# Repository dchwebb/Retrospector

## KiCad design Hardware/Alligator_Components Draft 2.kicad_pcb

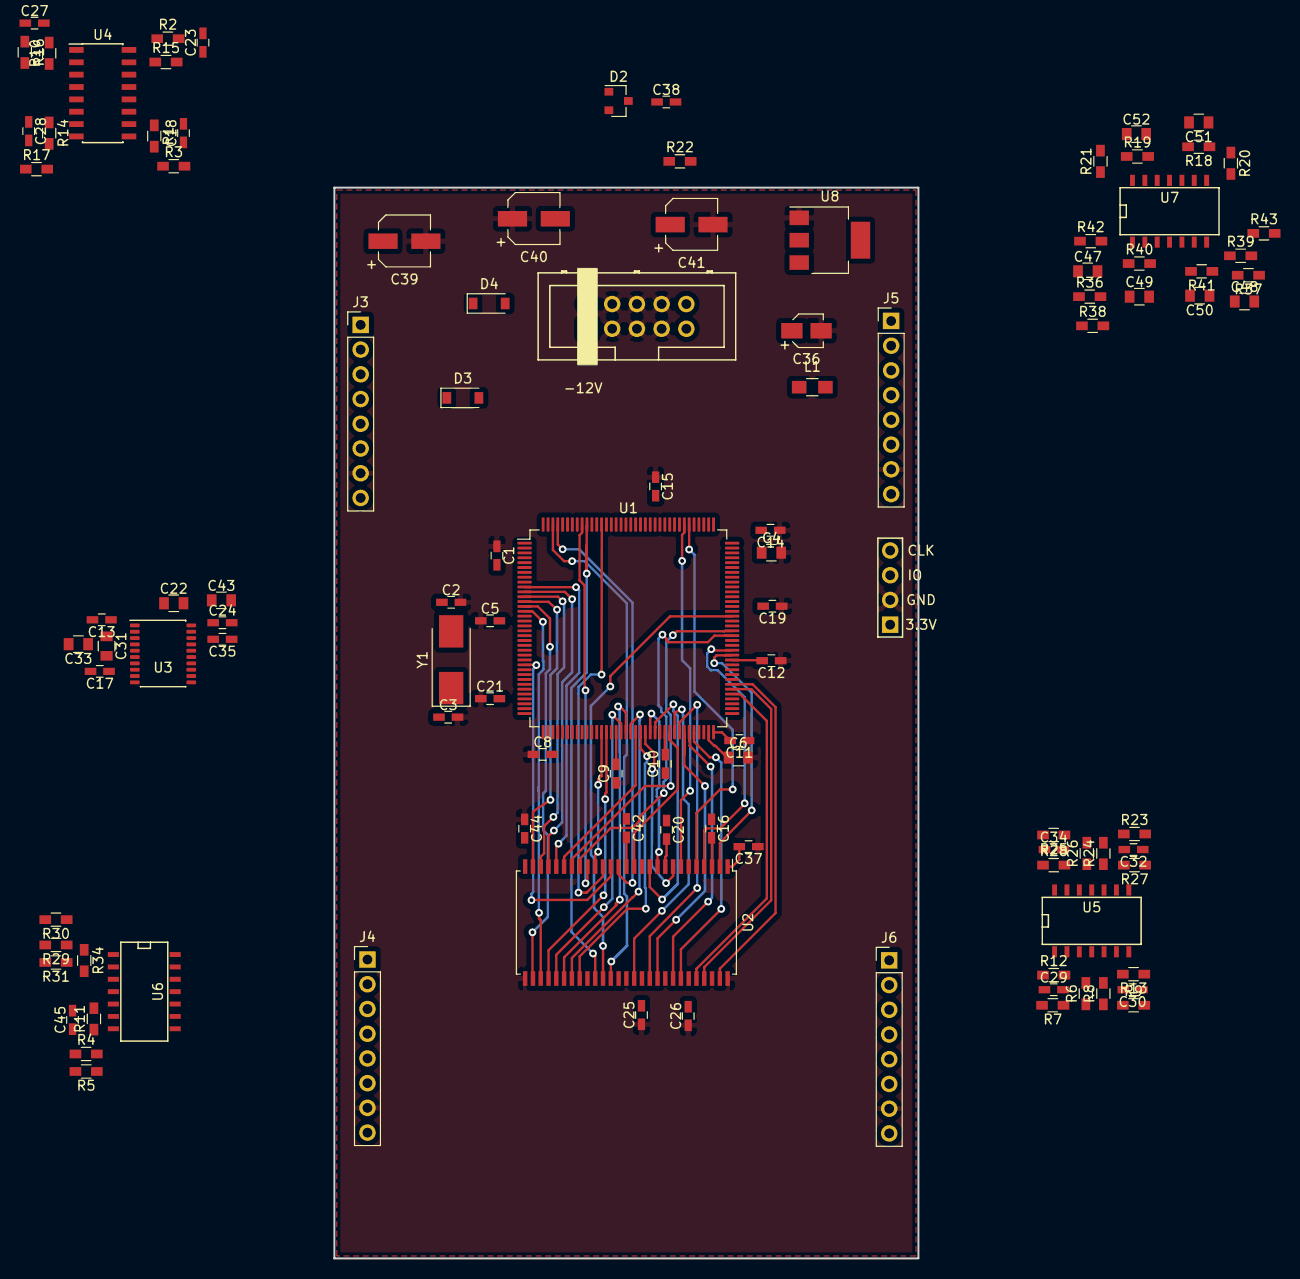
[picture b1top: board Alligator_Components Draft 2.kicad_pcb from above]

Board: 2 copper layers, 60.0 x 110.0 mm, 109 parts (0 on the bottom side), 118 nets.

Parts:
C1, C5, C8, C9, C10, C11, C12, C13, C14, C15, C16, C17, C19, C20, C21, C24, C25, C26, C35, C37, C38, C42, C44: 100nF; C_0603_HandSoldering
C2, C3: 30pF; C_0603_HandSoldering
C4, C6, C31, C33: 2.2uF; C_0805
C18, C23, C27, C28: 560pF; C_0603_HandSoldering
C22, C43: 10uF; C_0805
C29, C30, C32, C34, C45: 1.5nF; C_0603_HandSoldering
C36: 10uF; CP_Elec_3x5.3
C39, C40: 22uF; CP_Elec_5x5.3
C41: 47uF; CP_Elec_5x5.3
C47, C48: 1nF; C_0805
C49, C50, C51, C52: 100pF; C_0805
D2: LM4040DBZ-5; SOT-23
D3, D4: 1N5819; D_SOD-123
J1: SWD_Header; SWD_header
J2: Eurorack_10_pin_power; Eurorack_10_pin_header
J3, J4, J5, J6: Conn_01x08_Female; Socket_Strip_Straight_1x08_Pitch2.54mm
L1: L; L_0805_HandSoldering
R1, R2, R10, R14, R18, R19: 30k; R_0603_HandSoldering
R3, R15, R16, R17: 510R; R_0603_HandSoldering
R4, R30: 91k; R_0603_HandSoldering
R5, R24, R26: 100k; R_0603_HandSoldering
R6, R8: 20k; R_0603_HandSoldering
R7, R9, R27, R28, R31, R34: 47k; R_0603_HandSoldering
R11: 56k; R_0603_HandSoldering
R12, R13: 6k8; R_0603_HandSoldering
R20, R21, R42, R43: 1k; R_0603_HandSoldering
R22: 2.2k; R_0603_HandSoldering
R23, R25: 68k; R_0603_HandSoldering
R29: 75k; R_0603_HandSoldering
R36, R37: 2k2; R_0603_HandSoldering
R38, R39: 10k; R_0603_HandSoldering
R40, R41: 33k; R_0603_HandSoldering
U1: STM32H743ZITx; LQFP-144_20x20mm_P0.5mm
U2: IS42S16400J-xC; TSOP-II-54_22.2x10.16mm_P0.8mm
U3: PCM5100APW; SSOP-20_4.4x6.5mm_Pitch0.65mm_Round_Pads
U4: SSI2164; SOIC-16_3.9x9.9mm_Pitch1.27mm
U5, U6: MCP6004; SOIC-14_N
U7: TL074; SOIC-14_N
U8: LM1117-3.3; SOT-223
Y1: 8MHz 20pF; Crystal_SMD_0603-2pin_6.0x3.5mm_HandSoldering

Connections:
+3.3VA: C13.1, C17.1, C21.2, C22.1, J3.8, J4.8, J5.8, J6.8, L1.1, U1.32, U1.33, U1.143, U3.1, U3.8, U5.4, U6.4, U6.12
+3V3: C1.2, C5.2, C8.2, C9.2, C10.2, C11.2, C12.2, C14.2, C15.2, C16.2, C19.2, C20.2, C24.1, C25.2, C26.2, C37.2, C41.1, C42.2, C43.1, C44.2, J1.1, L1.2, U1.6, U1.17, U1.30, U1.39, U1.52, U1.62, U1.72, U1.84, U1.95, U1.108, U1.121, U1.131, U1.144, U2.1, U2.3, U2.9, U2.14, U2.27, U2.43, U2.49, U3.11, U3.17, U3.20, U8.2
+12V: D3.2, J2.9, J2.10
-12V: D4.1, J2.1, J2.2
/AUDIO_IN_L: C29.1, R1.2, R12.1, U1.42, U5.1
/AUDIO_IN_R: C30.1, R2.2, R13.1, U1.27, U5.7
/CLOCK: J4.6, U6.10
/CLOCK_SCALED: U6.8, U6.9
/DAC_BCLK: U1.69, U3.13
/DAC_DATA: U1.76, U3.14
/DAC_LRCLK: U1.140, U3.15
/DAC_OUT_AMP_L: R10.2, R42.1
/DAC_OUT_AMP_R: R14.2, R43.1
/DAC_OUT_L: R36.2, U3.6
/DAC_OUT_R: R37.2, U3.7
/DELAY_CV_L: J5.1, R24.2
/DELAY_CV_R: J5.3, R26.2, U1.34
/DELAY_CV_SCALED_L: C32.1, R27.1, U1.37, U5.8
/DELAY_CV_SCALED_R: C34.1, R28.1, U1.44, U5.14
/DELAY_POT_L: J5.2, U1.45
/DELAY_POT_R: J5.4, U1.35
/DRY_OUT_L: C51.2, R18.2, U4.4, U4.12, U7.9
/DRY_OUT_R: C52.2, R19.2, U4.5, U4.13, U7.13
/EXT_AUDIO_IN_L: J4.1, R7.2
/EXT_AUDIO_IN_R: J4.2, R9.2
/EXT_AUDIO_OUT_L: J4.4, R20.1
/EXT_AUDIO_OUT_R: J4.5, R21.1
/FEEDBACK_CV: J6.3, R5.2
/FEEDBACK_CV_SCALED: C45.1, R11.1, U1.43, U6.7
/FEEDBACK_POT: J6.4, U1.46
/FMC_A0: U1.10, U2.23
/FMC_A1: U1.11, U2.24
/FMC_A2: U1.12, U2.25
/FMC_A3: U1.13, U2.26
/FMC_A4: U1.14, U2.29
/FMC_A5: U1.15, U2.30
/FMC_A6: U1.50, U2.31
/FMC_A7: U1.53, U2.32
/FMC_A8: U1.54, U2.33
/FMC_A9: U1.55, U2.34
/FMC_A10: U1.56, U2.22
/FMC_A11: U1.57, U2.35
/FMC_BA0: U1.89, U2.20
/FMC_BA1: U1.90, U2.21
/FMC_D0: U1.85, U2.2
/FMC_D1: U1.86, U2.4
/FMC_D2: U1.114, U2.5
/FMC_D3: U1.115, U2.7
/FMC_D4: U1.58, U2.8
/FMC_D5: U1.59, U2.10
/FMC_D6: U1.60, U2.11
/FMC_D7: U1.63, U2.13
/FMC_D8: U1.64, U2.42
/FMC_D9: U1.65, U2.44
/FMC_D10: U1.66, U2.45
/FMC_D11: U1.67, U2.47
/FMC_D12: U1.68, U2.48
/FMC_D13: U1.77, U2.50
/FMC_D14: U1.78, U2.51
/FMC_D15: U1.79, U2.53
/FMC_SDCKE1: U1.135, U2.37
/FMC_SDCLK: U1.93, U2.38
/FMC_SD~E1: U1.136, U2.19
/FMC_SD~WE: U1.26, U2.16
/FMC_~BL0: U1.141, U2.15
/FMC_~BL1: U1.142, U2.39
/FMC_~CAS: U1.132, U2.17
/FMC_~RAS: U1.49, U2.18
/LED1: J6.5, U1.111
/LED2: J6.6, U1.112
/MIX_CV: J6.2, R30.2
/MIX_DRY_CTL: U1.40, U4.11, U4.14
/MIX_POT: J6.1, R31.2
/MIX_WET_CTL: U1.41, U4.3, U4.6
/MODE1: J3.2, U1.97
/MODE2: J3.3, U1.98
/RESET: J4.3, U1.25
/SWCLK: J1.4, U1.109
/SWIO: J1.3, U1.105
/USB_DM: J3.5, U1.103
/USB_DP: J3.6, U1.104
/USB_VBUS: J3.4, U1.101
/WET_DRY_MIX: R34.1, U1.47, U6.1
AREF_-5: C38.1, D2.2, R4.2, R6.2, R8.2, R22.2, R23.2, R25.2, R29.2
GND: C1.1, C2.2, C3.2, C4.2, C5.1, C6.2, C8.1, C9.1, C10.1, C11.1, C12.1, C13.2, C14.1, C15.1, C16.1, C17.2, C18.2, C19.1, C20.1, C21.1, C22.2, C23.2, C24.2, C25.1, C26.1, C27.2, C28.2, C33.2, C35.1, C36.2, C37.1, C38.2, C39.2, C40.1, C41.2, C42.1, C43.2, C44.1, C47.2, C48.2, D2.1, J1.2, J2.3, J2.4, J2.5, J2.6, J2.7, J2.8, J3.7, J4.7, J5.7, J6.7, U1.16, U1.31, U1.38, U1.51, U1.61, U1.83, U1.94, U1.107, U1.120, U1.130, U1.138, U2.6, U2.12, U2.28, U2.41, U2.46, U2.52, U2.54, U3.3, U3.9, U3.10, U3.12, U3.16, U3.19, U4.8, U5.3, U5.5, U5.10, U5.11, U5.12, U6.3, U6.5, U6.11, U7.3, U7.5, U7.10, U7.12, U8.1
unnamed: C2.1, U1.23, Y1.2
unnamed: C3.1, U1.24, Y1.1
unnamed: C4.1, U1.106
unnamed: C6.1, U1.71
unnamed: C18.1, R3.1
unnamed: C23.1, R15.1
unnamed: C27.1, R16.1
unnamed: C28.1, R17.1
unnamed: C29.2, R6.1, R7.1, R12.2, U5.2
unnamed: C30.2, R8.1, R9.1, R13.2, U5.6
unnamed: C31.1, U3.2
unnamed: C31.2, U3.4
unnamed: C32.2, R23.1, R24.1, R27.2, U5.9
unnamed: C33.1, U3.5
unnamed: C34.2, R25.1, R26.1, R28.2, U5.13
unnamed: C35.2, U3.18
unnamed: C45.2, R4.1, R5.1, R11.2, U6.6
unnamed: C47.1, R36.1, R38.2
unnamed: C48.1, R37.1, R39.2
unnamed: C49.1, R40.1, R42.2, U7.1
unnamed: C49.2, R38.1, R40.2, U7.2
unnamed: C50.1, R41.1, R43.2, U7.7
unnamed: C50.2, R39.1, R41.2, U7.6
unnamed: C51.1, R18.1, R20.2, U7.8
unnamed: C52.1, R19.1, R21.2, U7.14
unnamed: R1.1, R3.2, U4.10
unnamed: R10.1, R16.2, U4.2
unnamed: R14.1, R17.2, U4.7
unnamed: R2.1, R15.2, U4.15
unnamed: R29.1, R30.1, R31.1, R34.2, U6.2
unnamed: U6.13, U6.14
VCC: C36.1, C39.1, D3.1, U4.16, U7.11, U8.3
VEE: C40.2, D4.2, R22.1, U4.9, U7.4

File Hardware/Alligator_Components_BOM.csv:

"Comment","Designator","Footprint","LCSC Part #"
"100nF","C1, C5, C7, C8, C9, C10, C11, C12, C13, C14, C15, C16, C17, C19, C20, C21, C24, C25, C26, C35, C37, C38, C42, C44, C46, ","C_0603_HandSoldering","C14663"
"30pF","C2, C3, ","C_0603_HandSoldering","C22397"
"2.2uF","C4, C6, C31, C33, ","C_0805","C49217"
"560pF","C18, C23, C27, C28, ","C_0603_HandSoldering","C84721"
"10uF","C22, C43, ","C_0805","C15850 "
"1.5nF","C29, C30, C32, C34, C45, ","C_0603_HandSoldering","C1595"
"10uF","C36, ","CP_Elec_3x5.3","C249452"
"47uF","C41, ","CP_Elec_5x5.3","C134798"
"1nF","C47, C48, ","C_0805","C46653 "
"100pF","C49, C50, C51, C52, ","C_0805","C1790 "
"LM4040DBZ-5","D2, ","SOT-23","C69316"
"1N5819","D3, D4, ","D_SOD-123","C169540"
"L","L1, ","L_0805_HandSoldering","C1046"
"30k","R1, R2, R10, R14, R18, R19, ","R_0603_HandSoldering","C22984"
"510R","R3, R15, R16, R17, ","R_0603_HandSoldering","C23193"
"91k","R4, R30, ","R_0603_HandSoldering","C23265"
"100k","R5, R24, R26, ","R_0603_HandSoldering","C25803"
"20k","R6, R8, ","R_0603_HandSoldering","C4184 "
"47k","R7, R9, R27, R28, R31, R34, ","R_0603_HandSoldering","C25819"
"56k","R11, ","R_0603_HandSoldering","C23206"
"6k8","R12, R13, ","R_0603_HandSoldering","C23212 "
"1k","R20, R21, R42, R43, ","R_0603_HandSoldering","C21190"
"2k2","R22, R36, R37, ","R_0603_HandSoldering","C4190"
"68k","R23, R25, ","R_0603_HandSoldering","C23231"
"75k","R29, ","R_0603_HandSoldering","C23242 "
"330R","R32, R33, ","R_0603_HandSoldering","C23138"
"10k","R38, R39, ","R_0603_HandSoldering","C25804"
"33k","R40, R41, ","R_0603_HandSoldering","C4216 "
"STM32H743ZITx","U1, ","LQFP-144_20x20mm_P0.5mm","C114408"
"IS42S16400J-xC","U2, ","TSOP-II-54_22.2x10.16mm_P0.8mm","C69411"
"PCM5100APW","U3, ","SSOP-20_4.4x6.5mm_Pitch0.65mm_Round_Pads","C131154"
"MCP6004","U5, U6, ","SOIC-14_N","C7378"
"TL074","U7, ","SOIC-14_N","C6964"
"LM1117-3.3","U8, ","SOT-223","C6186"

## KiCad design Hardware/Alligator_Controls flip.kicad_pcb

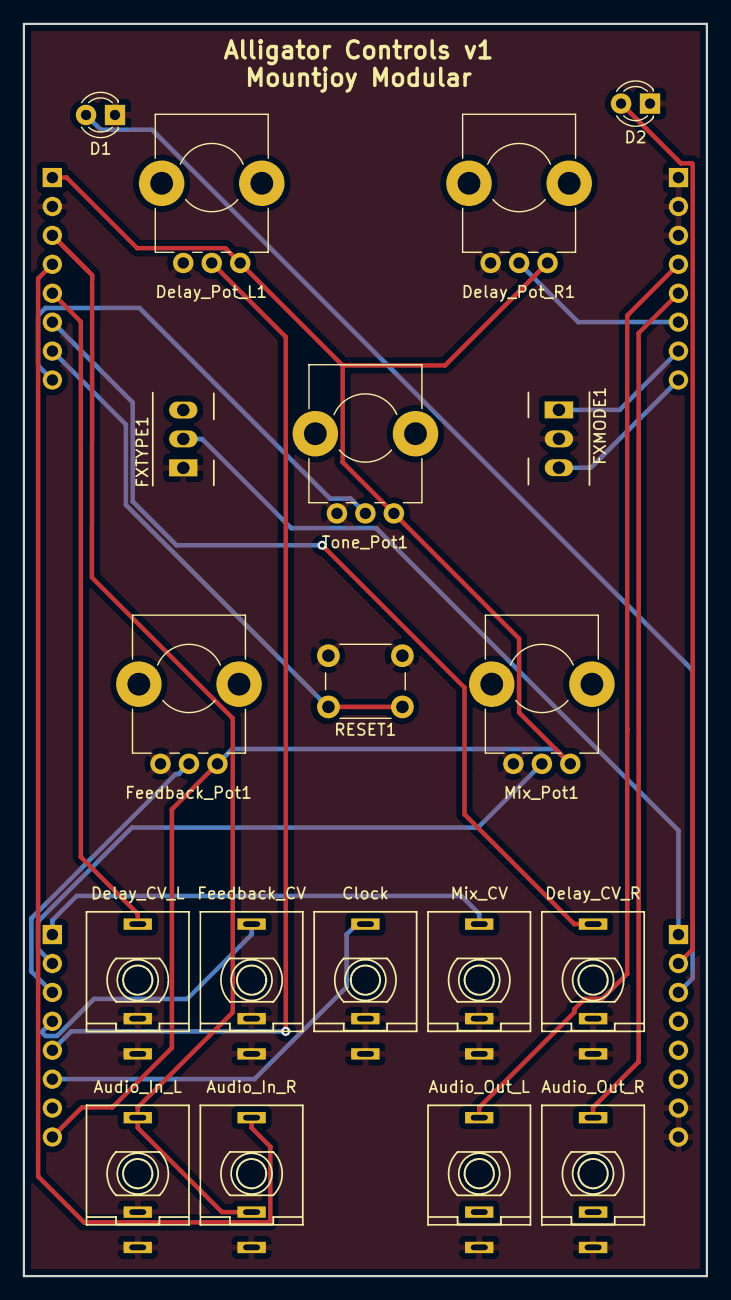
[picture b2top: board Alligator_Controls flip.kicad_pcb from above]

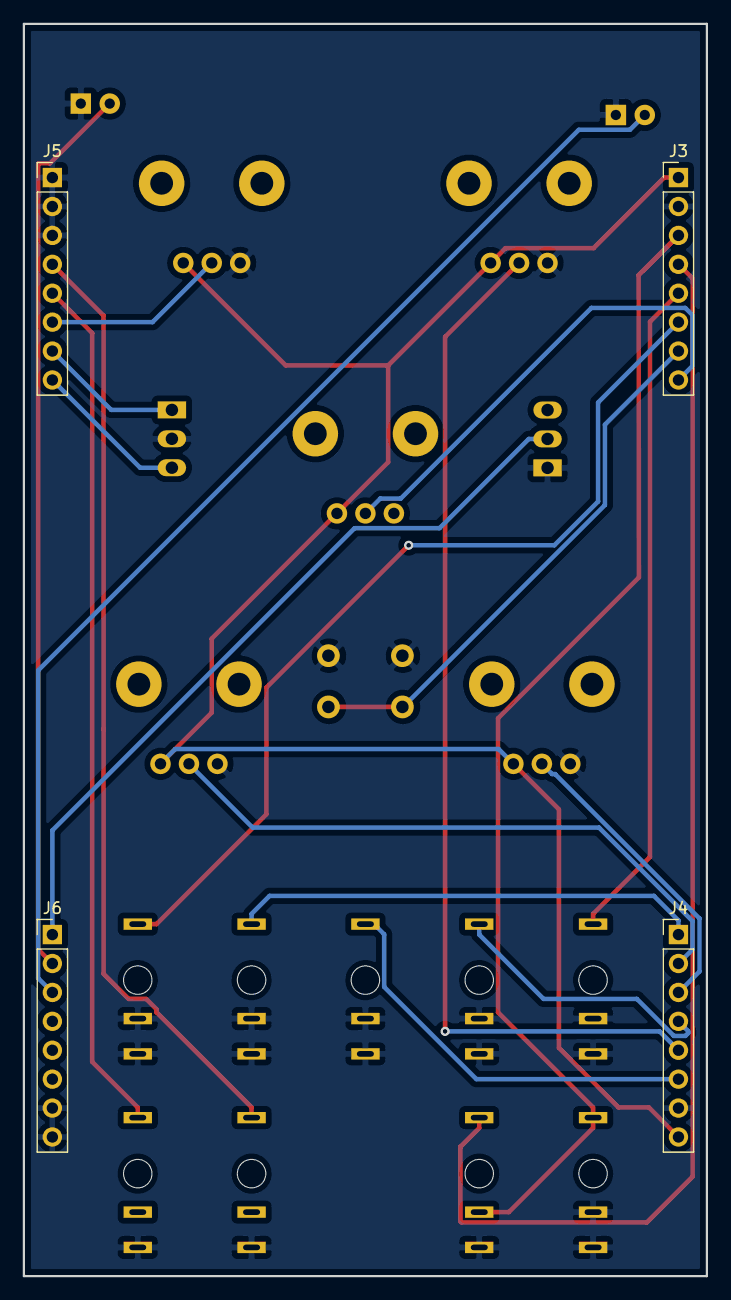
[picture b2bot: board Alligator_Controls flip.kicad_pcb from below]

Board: 2 copper layers, 60.0 x 110.0 mm, 23 parts (4 on the bottom side), 22 nets.

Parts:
D1, D2: LED; LED_D3.0mm
Delay_Pot_L1: A10k; Alpha_9mm_Potentiometer
Delay_Pot_R1: A10k; Alpha_9mm_Potentiometer
FXMODE1: SW_SPDT_MSM; SPDTSubMiniature
FXTYPE1: SW_SPST; SPDTSubMiniature
Feedback_Pot1: A10k; Alpha_9mm_Potentiometer
J1: Audio_In_L; THONKICONN_hole
J2: Delay_CV_L; THONKICONN_hole
J3, J4, J5, J6: Conn_01x08_Female; Socket_Strip_Straight_1x08_Pitch2.54mm
J7: Mix_CV; THONKICONN_hole
J8: Delay_CV_R; THONKICONN_hole
J9: Clock; THONKICONN_hole
J10: Feedback_CV; THONKICONN_hole
J11: Audio_In_R; THONKICONN_hole
J12: Audio_Out_R; THONKICONN_hole
J13: Audio_Out_L; THONKICONN_hole
Mix_Pot1: A10k; Alpha_9mm_Potentiometer
RESET1: SW_Push; SW_PUSH_6mm
Tone_Pot1: A10k; Alpha_9mm_Potentiometer

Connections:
+3.3VA: Delay_Pot_L1.1, Delay_Pot_R1.1, Feedback_Pot1.1, J3.1, J4.8, Mix_Pot1.1, Tone_Pot1.1
/CLOCK: J4.6, J9.3
/DELAY_CHORUS: FXTYPE1.2, J6.1
/DELAY_CV_L: J2.3, J3.5
/DELAY_CV_R: J3.6, J8.3
/DELAY_POT_L: Delay_Pot_L1.2, J4.5
/DELAY_POT_R: Delay_Pot_R1.2, J5.6
/EXT_AUDIO_IN_L: J1.3, J3.3, J11.2
/EXT_AUDIO_IN_R: J3.4, J11.3
/EXT_AUDIO_OUT_L: J5.4, J13.3
/EXT_AUDIO_OUT_R: J5.5, J12.3
/FEEDBACK_CV: J4.4, J10.3
/FEEDBACK_POT: Feedback_Pot1.2, J4.3
/LED1: D1.2, J6.3
/LED2: D2.2, J6.2
/MIX_CV: J4.1, J7.3
/MIX_POT: J4.2, Mix_Pot1.2
/MODE1: FXMODE1.1, J5.7
/MODE2: FXMODE1.3, J5.8
/RESET: J3.7, RESET1.1
/TONE_POT: J3.8, Tone_Pot1.2
GND: D1.1, D2.1, Delay_Pot_L1.3, Delay_Pot_R1.3, FXMODE1.2, FXTYPE1.1, Feedback_Pot1.3, J1.1, J1.2, J2.1, J2.2, J3.2, J4.7, J5.1, J5.2, J5.3, J6.7, J6.8, J7.1, J7.2, J8.1, J8.2, J9.1, J9.2, J10.1, J10.2, J11.1, J12.1, J13.1, Mix_Pot1.3, RESET1.2, Tone_Pot1.3
